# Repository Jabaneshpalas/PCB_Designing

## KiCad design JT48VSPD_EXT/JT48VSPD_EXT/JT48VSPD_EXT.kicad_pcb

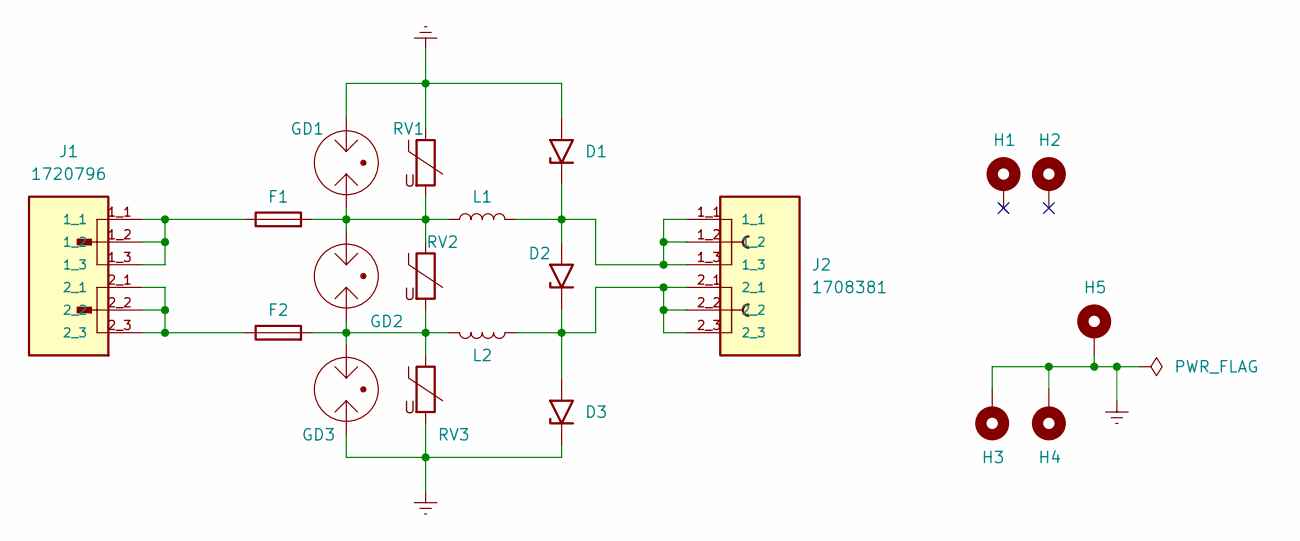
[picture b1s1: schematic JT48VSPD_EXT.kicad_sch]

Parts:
D1, D2, D3: 5.0SMDJ75A; DIOM7959X262N
F1, F2: Fuse; Fuseholder_Littelfuse_100_series_5x25mm
GD1, GD2, GD3: B88069X4760T902; MOV_B88069X4760T902
H1, H2, H3, H4, H5: MountingHole_Pad; MountingHole_3mm_Pad_TopBottom
J1: 1720796; PHOENIX_1720796; PARTREV 18.07.2018
J2: 1708381; PHOENIX_1708381; PARTREV 15.06.2015
L1, L2: L; EE16-SS-1
RV1, RV2, RV3: V100ZA15P; VARRB750W81L1700T500H2250

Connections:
Earth: D1.2 (A2), D3.1 (A1), GD1.3, GD3.1, H3.1, H4.1, H5.1, RV1.1, RV3.2
unnamed: D1.1 (A1), D2.2 (A2), J2.1_1, J2.1_2, J2.1_3, L1.2
unnamed: D2.1 (A1), D3.2 (A2), J2.2_1, J2.2_2, J2.2_3, L2.2
unnamed: F1.1, J1.1_1, J1.1_2, J1.1_3
unnamed: F1.2, GD1.1, GD2.3, L1.1, RV1.2, RV2.1
unnamed: F2.1, J1.2_1, J1.2_2, J1.2_3
unnamed: F2.2, GD2.1, GD3.3, L2.1, RV2.2, RV3.1

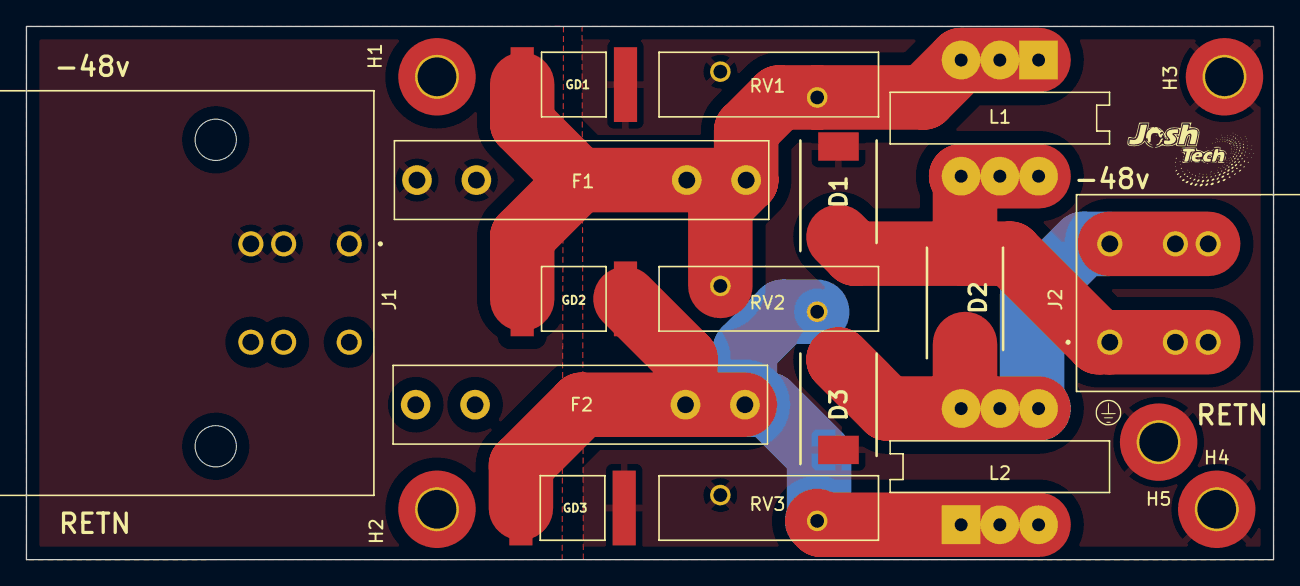
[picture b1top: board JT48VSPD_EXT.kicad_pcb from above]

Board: 2 copper layers, 96.6 x 41.3 mm, 20 parts (0 on the bottom side), 7 nets.

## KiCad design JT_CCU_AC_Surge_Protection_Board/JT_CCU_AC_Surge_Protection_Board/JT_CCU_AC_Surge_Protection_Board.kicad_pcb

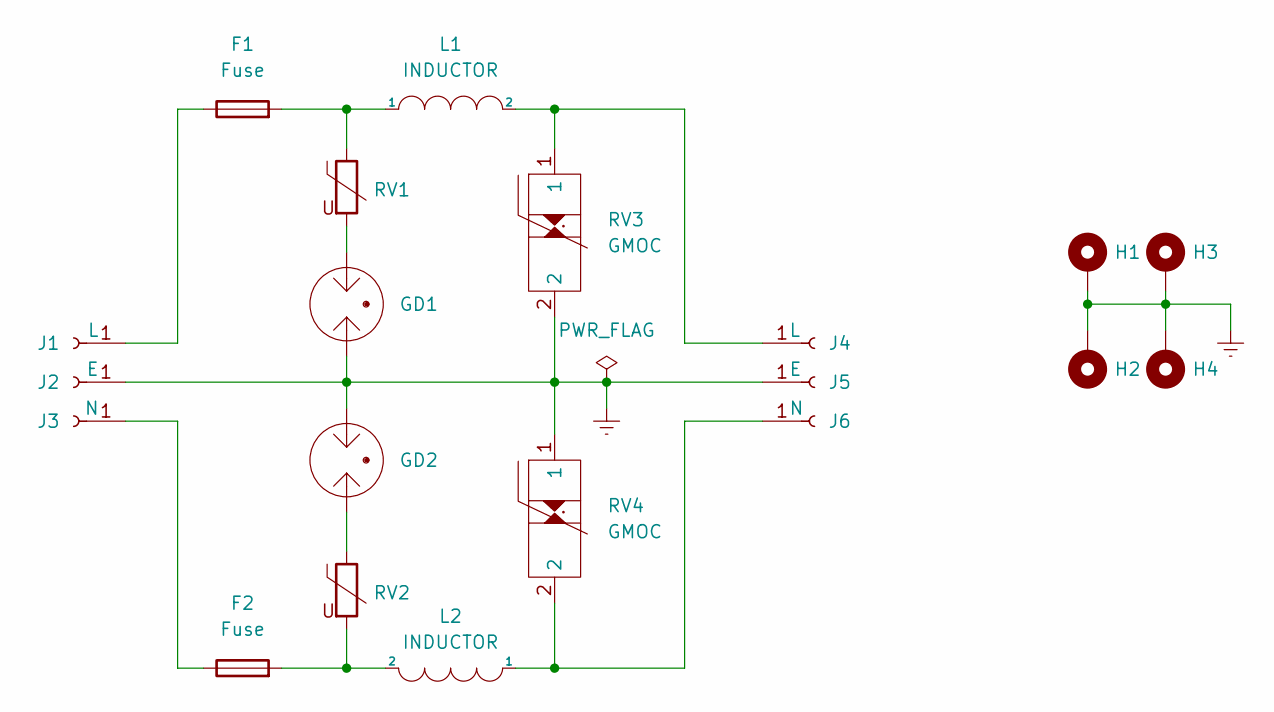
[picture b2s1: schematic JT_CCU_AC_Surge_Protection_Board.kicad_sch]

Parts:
F1, F2: Fuse
GD1, GD2: GDT_2Pin; GD Tube
H1, H2, H3, H4: MountingHole_Pad; CCU_GND_PT
J1: L; quickfit_PCB
J2: E; quickfit_PCB
J3: N; quickfit_PCB
J4: L; Out_conn
J5: E; Out_conn
J6: N; Out_conn
L1, L2: INDUCTOR; EE16-SS-1
RV1, RV2: Varistor; MOV20D391KKTR
RV3, RV4: GMOC; GMOV20D251K

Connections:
Earth: GD1.1, GD2.3, H1.1, H2.1, H3.1, H4.1, J2.1, J5.1, RV3.2, RV4.1
unnamed: F1.1, J1.1
unnamed: F1.2, L1.1, RV1.1
unnamed: F2.1, J3.1
unnamed: F2.2, L2.2, RV2.2
unnamed: GD1.3, RV1.2
unnamed: GD2.1, RV2.1
unnamed: J4.1, L1.2, RV3.1
unnamed: J6.1, L2.1, RV4.2

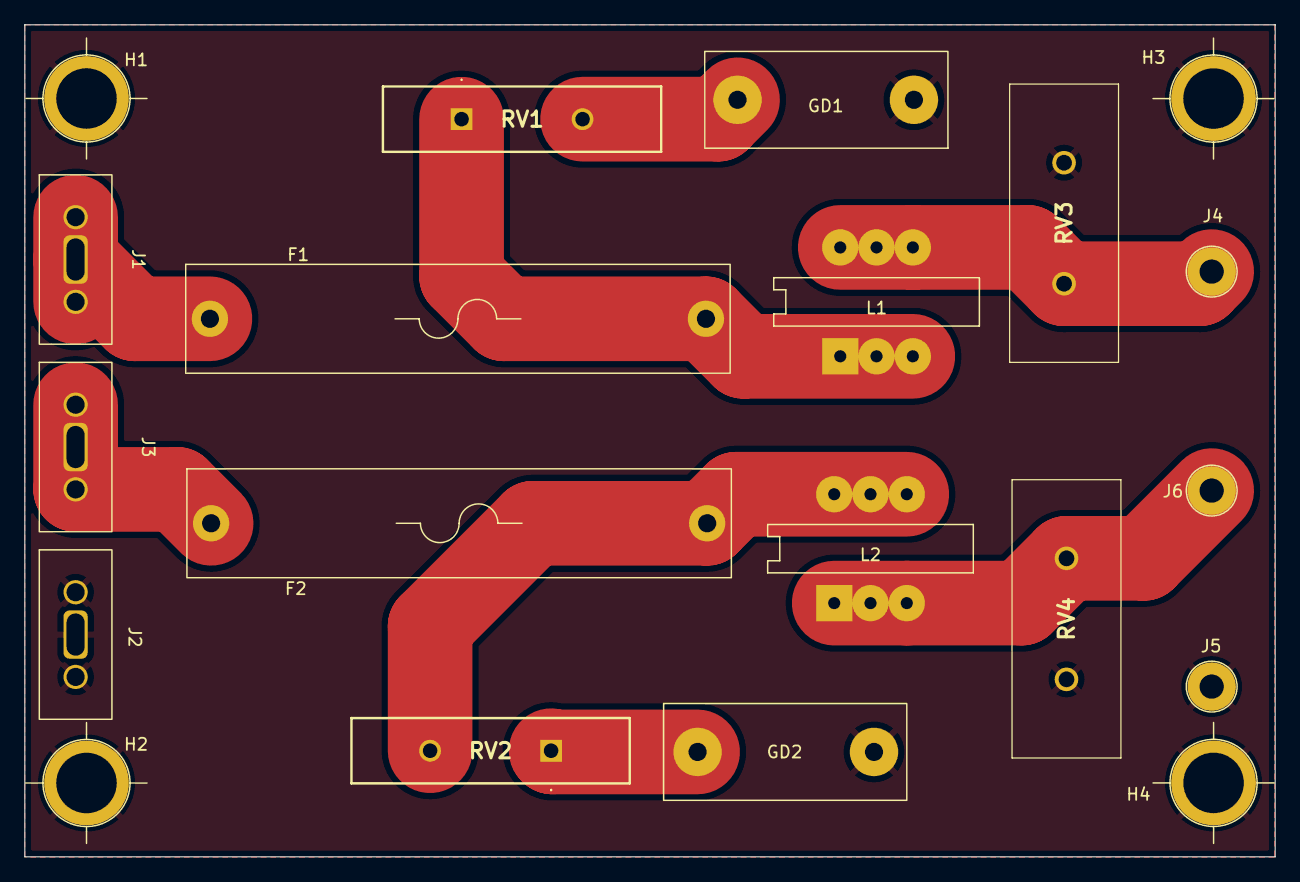
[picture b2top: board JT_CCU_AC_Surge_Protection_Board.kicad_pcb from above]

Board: 2 copper layers, 103.4 x 68.8 mm, 20 parts (0 on the bottom side), 9 nets.

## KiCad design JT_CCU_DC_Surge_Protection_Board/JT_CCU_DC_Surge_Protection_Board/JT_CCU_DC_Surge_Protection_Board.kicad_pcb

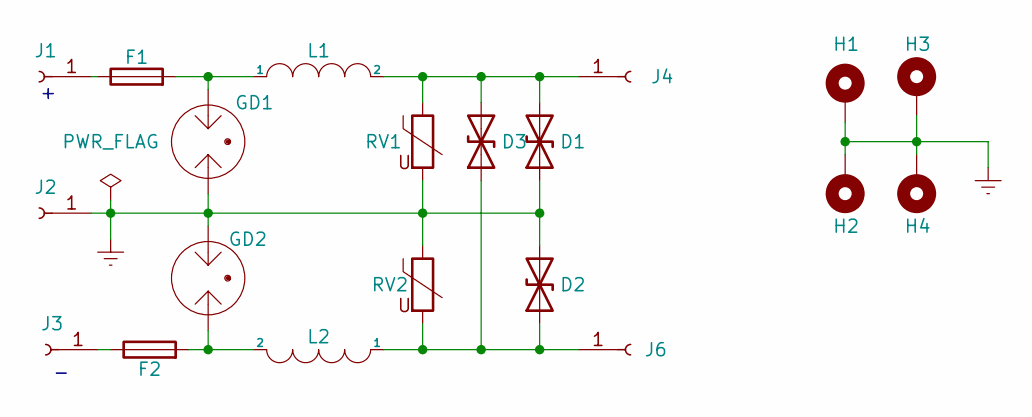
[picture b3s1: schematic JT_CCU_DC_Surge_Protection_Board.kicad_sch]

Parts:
D1, D2, D3: D_TVS; DIOAD1936W88L640D324
F1, F2: Fuse
GD1, GD2: GDT_2Pin; GD Tube
H1, H2, H3, H4: MountingHole_Pad; CCU_GND_PT
J1, J2, J3: Conn_01x01_Female; quickfit_PCB
J4, J6: Conn_01x01_Female; Out_conn
L1, L2: INDUCTOR; EE-25-SS-1
RV1, RV2: Varistor; VARRB750W100L2050T1200H2800

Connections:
Earth: D1.1 (A1), D2.2 (A2), GD1.1, GD2.3, H1.1, H2.1, H3.1, H4.1, J2.1, RV1.2, RV2.1
unnamed: D1.2 (A2), D3.2 (A2), J4.1, L1.2, RV1.1
unnamed: D2.1 (A1), D3.1 (A1), J6.1, L2.1, RV2.2
unnamed: F1.1, J1.1
unnamed: F1.2, GD1.3, L1.1
unnamed: F2.1, J3.1
unnamed: F2.2, GD2.1, L2.2

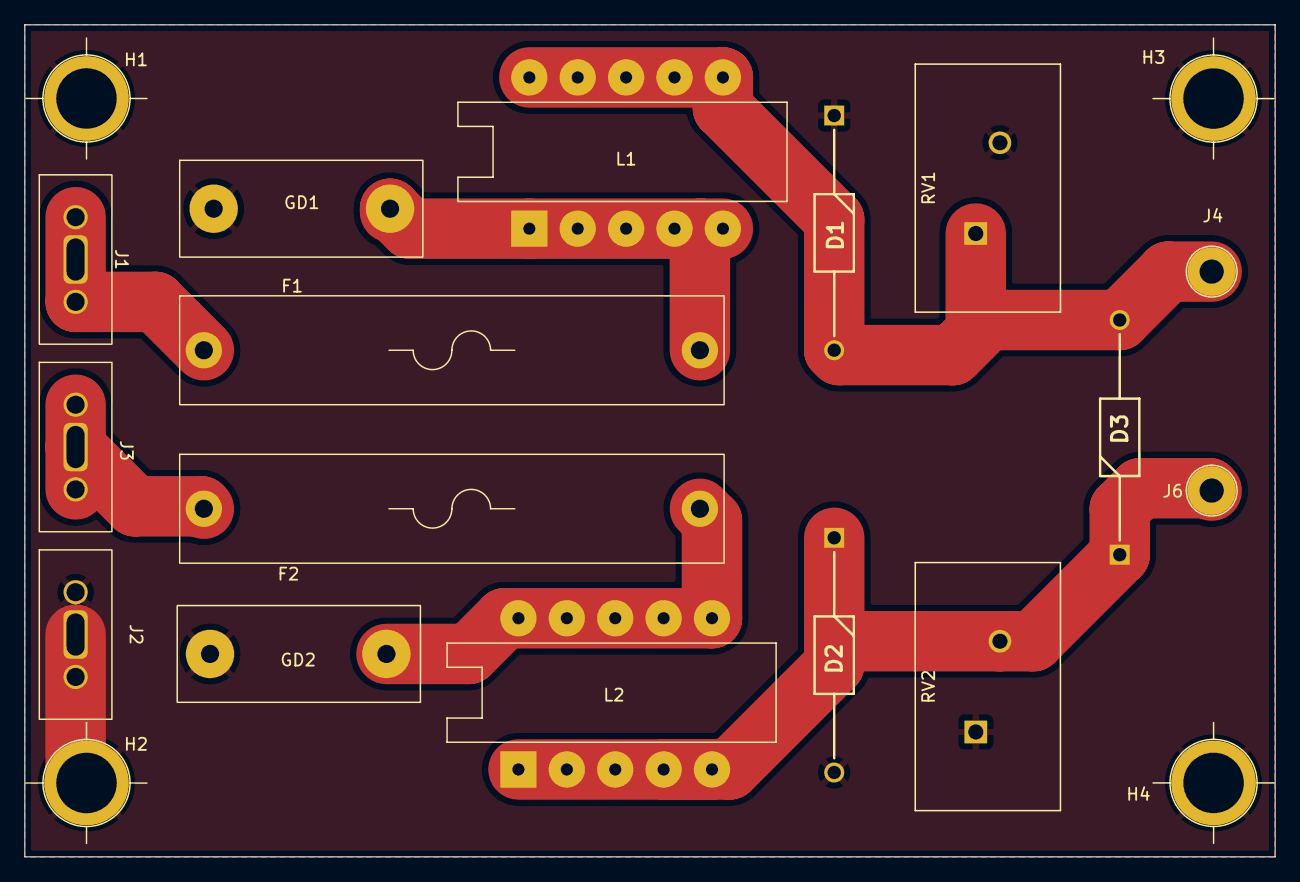
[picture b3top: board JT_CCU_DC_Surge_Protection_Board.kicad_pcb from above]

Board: 2 copper layers, 103.4 x 68.8 mm, 20 parts (0 on the bottom side), 7 nets.

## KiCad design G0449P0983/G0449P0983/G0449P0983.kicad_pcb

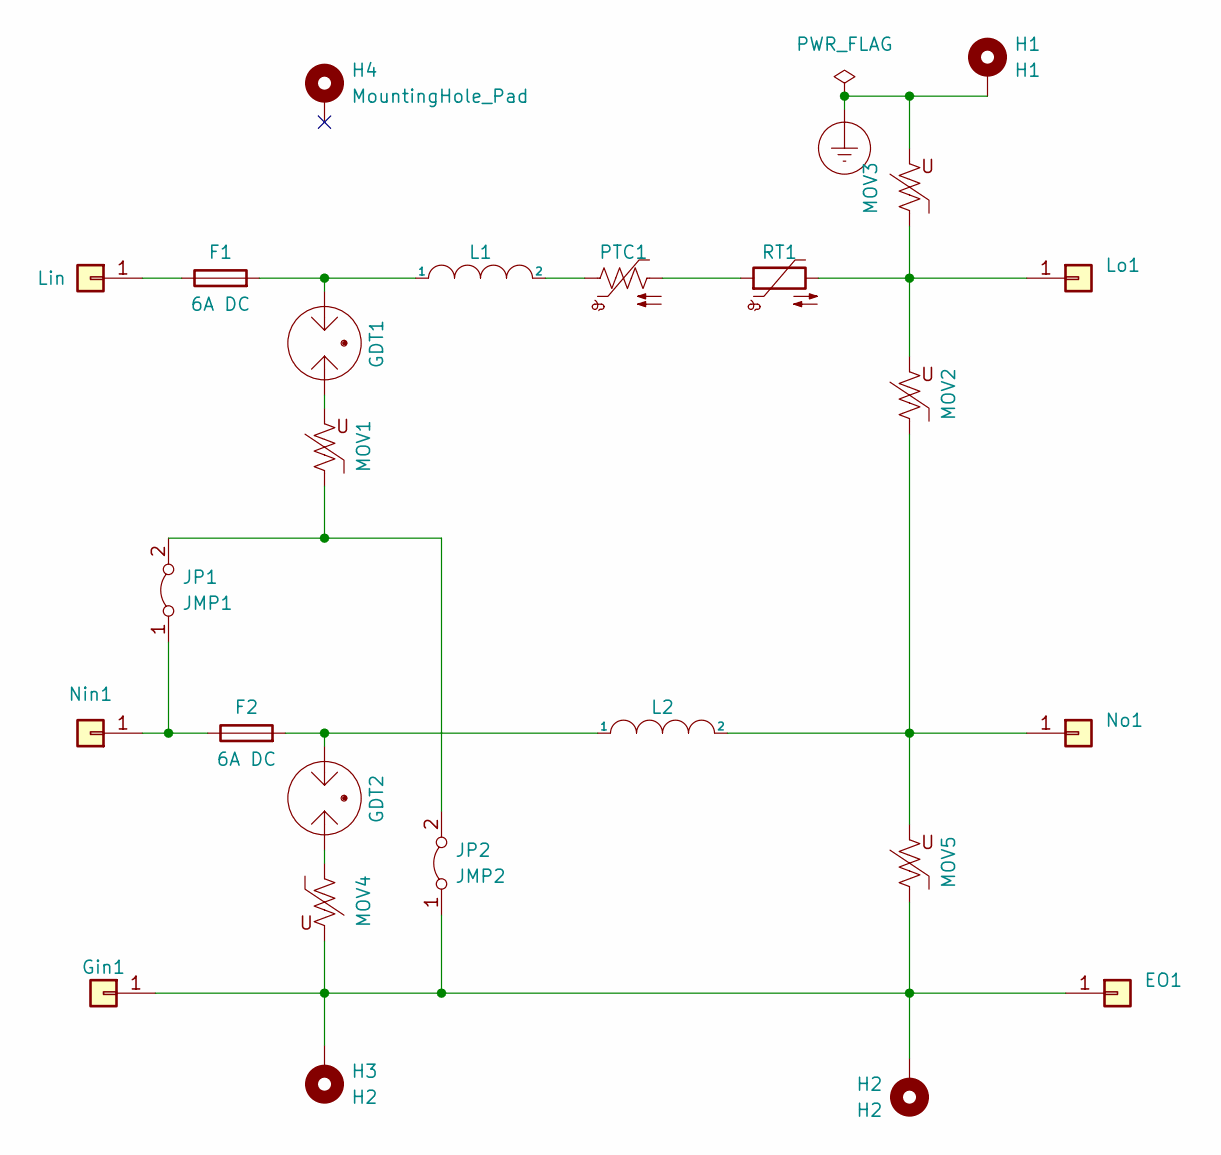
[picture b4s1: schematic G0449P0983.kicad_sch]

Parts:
EO1: Eo; Out_conn
F1, F2: 6A DC; Fuse_holder
GDT1: GDT1; CCU_GDT
GDT2: GDT2; CCU_GDT
Gin1: Gin; quickfit_PCB
H1: H1; CCU_GND_PT
H2, H3: H2; CCU_GND_PT
H4: MountingHole_Pad; CCU_GND_PT
JP1: JMP1; Jump1
JP2: JMP2; Jump2
L1: L1; CCU_IND
L2: L2; CCU_IND
Lin1: Lin; quickfit_PCB
Lo1: Lo; Out_conn
MOV1: MOV1; CCU_Vari_1
MOV2: MOV2; CCU_Vari
MOV3: MOV3; CCU_Vari
MOV4: MOV4; CCU_Vari_1
MOV5: MOV5; CCU_Vari
Nin1: Nin; quickfit_PCB
No1: No; Out_conn
PTC1: PTC; CCU_PTC
RT1: RT1; CCU_RTI

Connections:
Earth_Protective: H1.1, MOV3.2
unnamed: EO1.1, Gin1.1, H2.1, H3.1, JP2.1 (A), MOV4.2, MOV5.1
unnamed: F1.1, Lin1.1
unnamed: F1.2, GDT1.3, L1.1
unnamed: F2.1, JP1.1 (A), Nin1.1
unnamed: F2.2, GDT2.3, L2.1
unnamed: GDT2.1, MOV4.1
unnamed: JP1.2 (B), JP2.2 (B), MOV1.1
unnamed: L1.2, PTC1.1
unnamed: L2.2, MOV2.1, MOV5.2, No1.1
unnamed: Lo1.1, MOV2.2, MOV3.1, RT1.2
unnamed: GDT1.1, MOV1.2
unnamed: PTC1.2, RT1.1

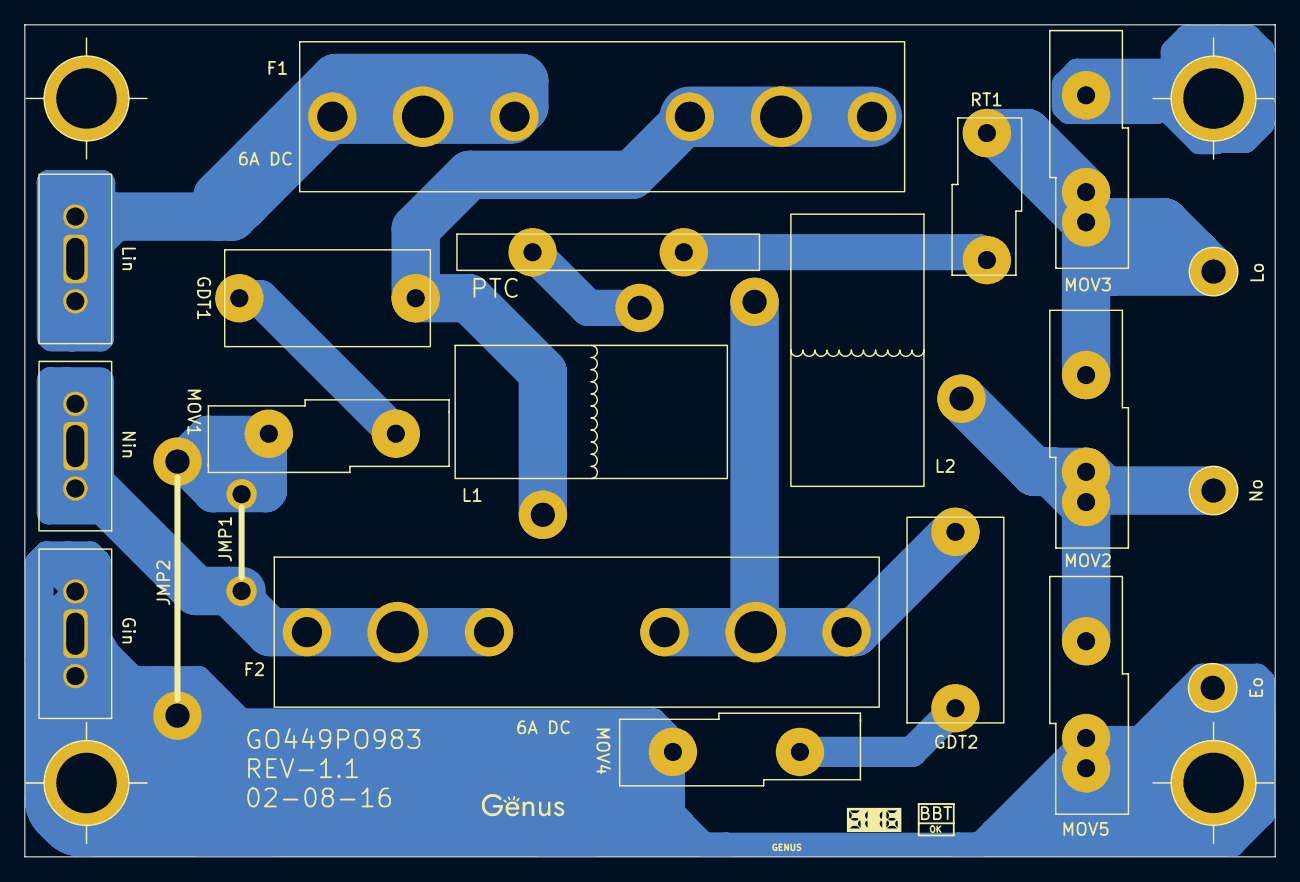
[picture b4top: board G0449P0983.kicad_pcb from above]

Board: 2 copper layers, 103.3 x 68.8 mm, 25 parts (0 on the bottom side), 13 nets.

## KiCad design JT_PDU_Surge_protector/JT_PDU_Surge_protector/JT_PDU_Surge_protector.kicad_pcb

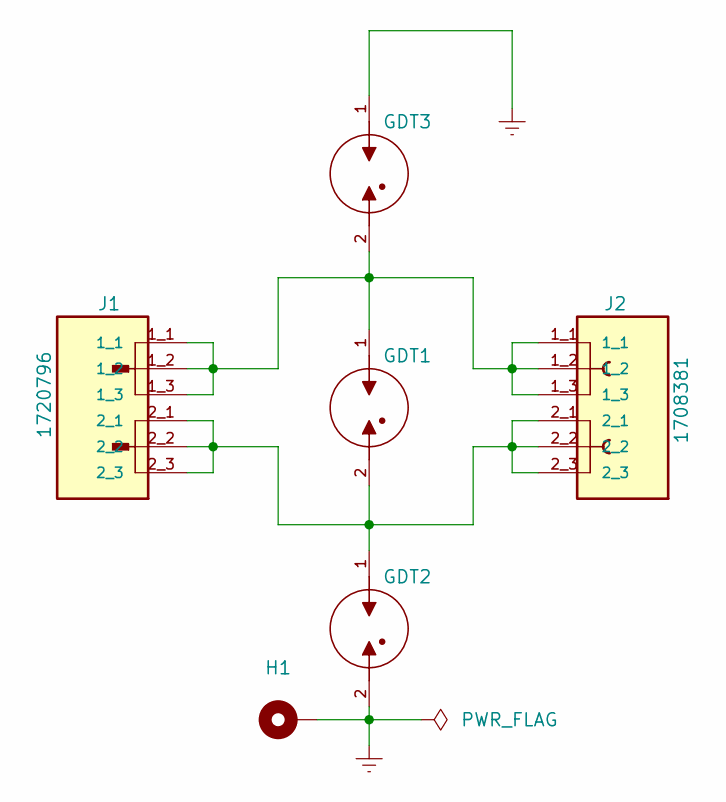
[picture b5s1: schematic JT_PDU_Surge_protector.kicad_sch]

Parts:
GDT1, GDT2, GDT3: B88069X4760T902; MOV_B88069X4760T902; PARTREV 7/29/2022
H1: MountingHole_Pad; MountingHole_3.2mm_M3_DIN965_Pad
J1: 1720796; PHOENIX_1720796; PARTREV 18.07.2018
J2: 1708381; PHOENIX_1708381; PARTREV 15.06.2015

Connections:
Earth: GDT2.2, GDT3.1, H1.1
unnamed: GDT1.1, GDT3.2, J1.1_1, J1.1_2, J1.1_3, J2.1_1, J2.1_2, J2.1_3
unnamed: GDT1.2, GDT2.1, J1.2_1, J1.2_2, J1.2_3, J2.2_1, J2.2_2, J2.2_3

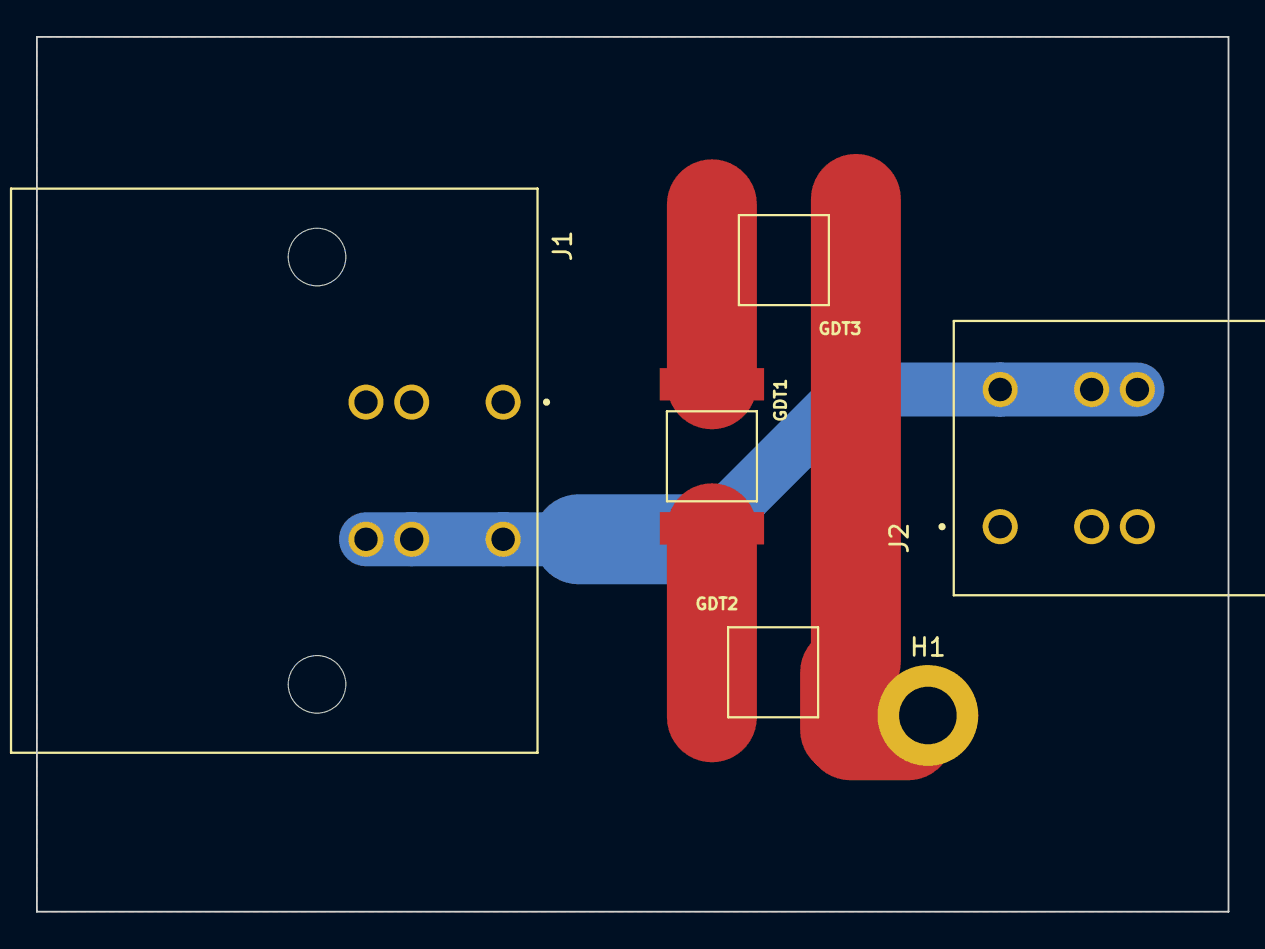
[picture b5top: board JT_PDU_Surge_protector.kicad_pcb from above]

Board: 2 copper layers, 66.2 x 48.6 mm, 6 parts (0 on the bottom side), 3 nets.

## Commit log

2024-06-21 second commit
2024-06-21 21.06.24 commit
2024-06-27 27.06.24 commit
2024-06-28 28.06.24 commit
